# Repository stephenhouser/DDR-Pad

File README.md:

---
category: woodworking
---

## Todo

- √ Clear acrylic ~ 12x12x 0.354 @ 10 = 180 + $50 shipping
 - https://www.tapplastics.com/product/plastics/cut_to_size_plastic/polycarbonate_sheets/516
 - 2024/01/01 - orderd 10 11x11x0.354" (3/8")
 - $229.94
- √ M6 Screws, M6 Nylon nuts -- Granger
 - 2024/01/03 Picked up nuts, screws on backorder to 2024/01/08
 - $60
	
- Decals ~ $70
 - https://www.bannerbuzz.com/clear-window-decals/p

- Arduino/teensy -- will it be fast enough?
 - perhaps microcontrollers at each pad sending data and lights?

- Metal corners?
 - 16 gague, need sheet brake (Rex?)

- 1.25" SteelTex no-thread pipe -- will it be sturdy enough
 - 1.25 is only in silver color
 - 2 bases, 2 90-deg, 3 poles

## The Build we are working from

- The hardware: [DIY Arcade DDR Metal Dance Pad With LED Under $500](https://www.instructables.com/DIY-Arcade-DDR-Metal-Dance-Pad-With-LED-Under-500/)
- The electronics: [6 Panel DDR USB Controller With LED](https://www.instructables.com/6-Panel-DDR-USB-Controller-With-LED/)

## Other Builds

- [Mystic Steps build](https://www.mysticsteps.com/diy-pad/), uses a AtMega32U (32u chipset for USB I imagine)
- [andrewhlu's build](https://andrewhlu.com/ddr/), uses [STM32L476G board](https://www.digikey.com/en/products/detail/stmicroelectronics/STM32L476G-DISCO/5344355)
- [Sensor Channels](https://www.thingiverse.com/thing:4547247) on Thingiverse, replacements for original DDR

## Making Pads

- https://www.hackmycab.com/?portfolio=arrow-panels-part-1-making-new-polycarb-panels
- https://www.hackmycab.com/?portfolio=arrow-panels-part-2-arrow-decals

## Lights

- [8x6 Lights](https://ddrpad.com/collections/arcade-parts/products/arcade-pad-led-light-mod) for original DDR
- [8x8 addressable LED modules](https://www.amazon.com/WS2812B-Flexible-Individually-Addressable-64Pixels/dp/B09KBZT6LD/ref=sr_1_4?crid=2BYV3RSFGN8D9&keywords=addressable%2Brgb%2Bled%2Bpanel&qid=1704314467&sprefix=addressable%2Brgb%2Bled%2Bpanel%2Caps%2C105&sr=8-4&th=1) from Amazon
 - ws2812 should be able to do about 64fps with 512 in a chain.
 - will need power injection at each row?
 - https://electronics.stackexchange.com/questions/338248/ws2812b-response-time

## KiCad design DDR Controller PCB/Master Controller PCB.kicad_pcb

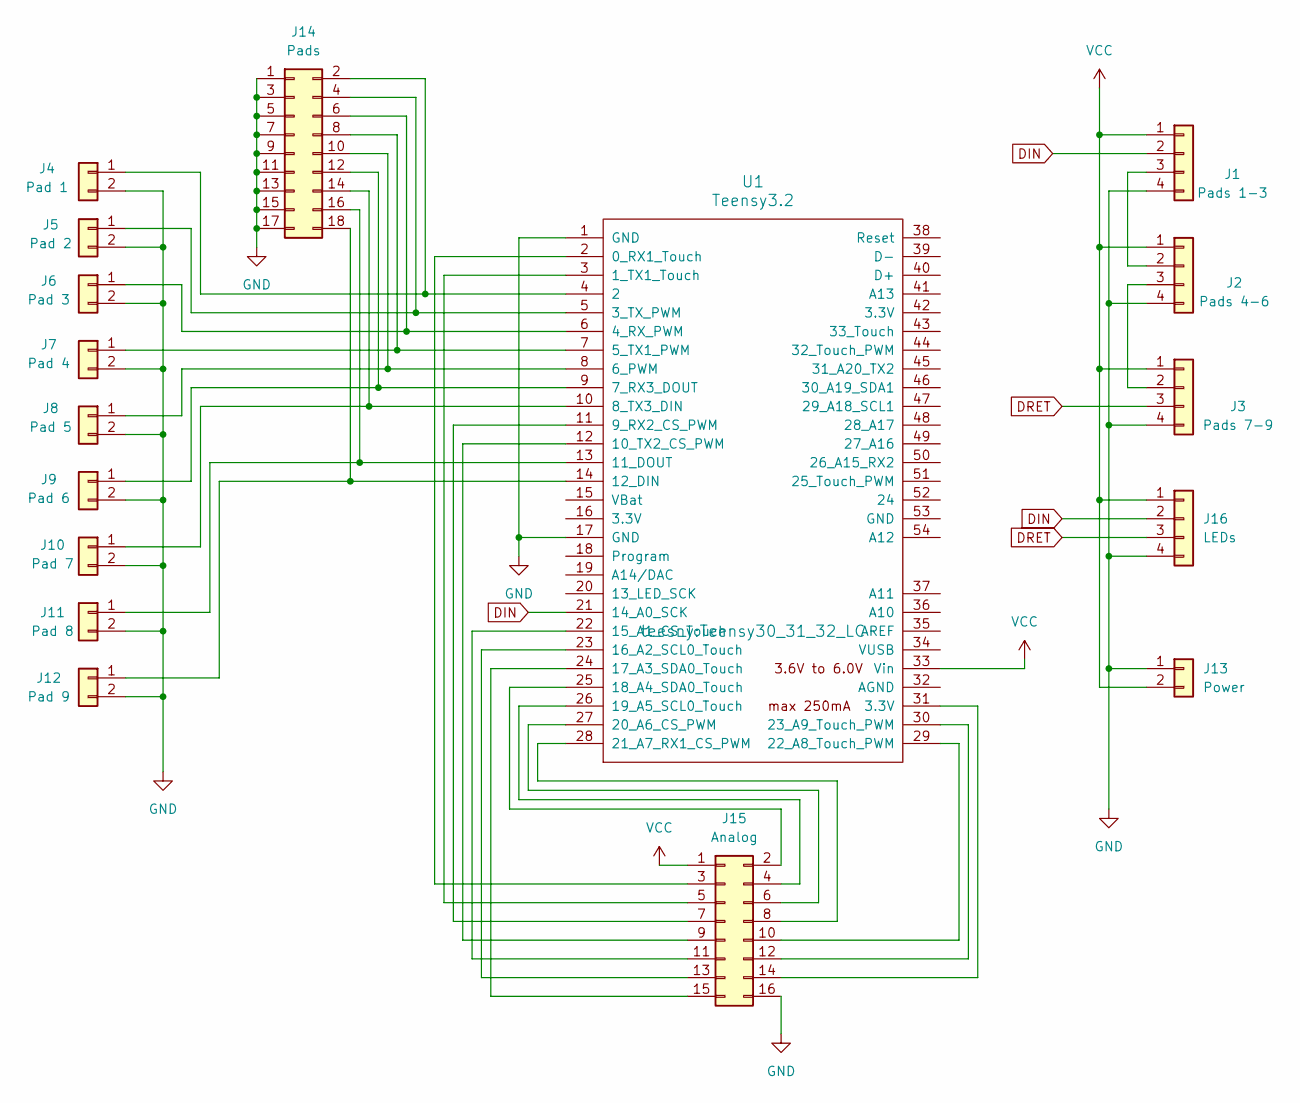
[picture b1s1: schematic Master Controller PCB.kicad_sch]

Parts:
J1: Pads 1-3; JST_XH_B4B-XH-A_1x04_P2.50mm_Vertical
J2: Pads 4-6; JST_XH_B4B-XH-A_1x04_P2.50mm_Vertical
J3: Pads 7-9; JST_XH_B4B-XH-A_1x04_P2.50mm_Vertical
J4: Pad 1; JST_XH_B2B-XH-A_1x02_P2.50mm_Vertical
J5: Pad 2; JST_XH_B2B-XH-A_1x02_P2.50mm_Vertical
J6: Pad 3; JST_XH_B2B-XH-A_1x02_P2.50mm_Vertical
J7: Pad 4; JST_XH_B2B-XH-A_1x02_P2.50mm_Vertical
J8: Pad 5; JST_XH_B2B-XH-A_1x02_P2.50mm_Vertical
J9: Pad 6; JST_XH_B2B-XH-A_1x02_P2.50mm_Vertical
J10: Pad 7; JST_XH_B2B-XH-A_1x02_P2.50mm_Vertical
J11: Pad 8; JST_XH_B2B-XH-A_1x02_P2.50mm_Vertical
J12: Pad 9; JST_XH_B2B-XH-A_1x02_P2.50mm_Vertical
J13: Power; screw_terminal_01x02_p7.62mm
J14: Pads; PinHeader_2x09_P2.54mm_Vertical
J15: Analog; PinHeader_2x08_P2.54mm_Vertical
J16: LEDs; PinHeader_1x04_P2.54mm_Vertical
U1: Teensy3.2; Teensy30_31_32_LC

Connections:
DIN: J1.2, J16.2, U1.21 (14_A0_SCK)
DRET: J3.3, J16.3
GND: J1.4, J2.4, J3.4, J4.2, J5.2, J6.2, J7.2, J8.2, J9.2, J10.2, J11.2, J12.2, J13.1, J14.1, J14.3, J14.5, J14.7, J14.9, J14.11, J14.13, J14.15, J14.17, J15.16, J16.4, U1.1 (GND), U1.17 (GND)
unnamed: J1.3, J2.2
unnamed: J2.3, J3.2
unnamed: J10.1, J14.14, U1.10 (8_TX3_DIN)
unnamed: J11.1, J14.16, U1.13 (11_DOUT)
unnamed: J12.1, J14.18, U1.14 (12_DIN)
unnamed: J4.1, J14.2, U1.4 (2)
unnamed: J5.1, J14.4, U1.5 (3_TX_PWM)
unnamed: J6.1, J14.6, U1.6 (4_RX_PWM)
unnamed: J7.1, J14.8, U1.7 (5_TX1_PWM)
unnamed: J8.1, J14.10, U1.8 (6_PWM)
unnamed: J9.1, J14.12, U1.9 (7_RX3_DOUT)
unnamed: J15.2, U1.25 (18_A4_SDA0_Touch)
unnamed: J15.3, U1.2 (0_RX1_Touch)
unnamed: J15.4, U1.26 (19_A5_SCL0_Touch)
unnamed: J15.5, U1.3 (1_TX1_Touch)
unnamed: J15.6, U1.27 (20_A6_CS_PWM)
unnamed: J15.7, U1.11 (9_RX2_CS_PWM)
unnamed: J15.8, U1.28 (21_A7_RX1_CS_PWM)
unnamed: J15.9, U1.12 (10_TX2_CS_PWM)
unnamed: J15.10, U1.29 (22_A8_Touch_PWM)
unnamed: J15.11, U1.22 (15_A1_CS_Touch)
unnamed: J15.12, U1.30 (23_A9_Touch_PWM)
unnamed: J15.13, U1.23 (16_A2_SCL0_Touch)
unnamed: J15.14, U1.31 (3.3V)
unnamed: J15.15, U1.24 (17_A3_SDA0_Touch)
VCC: J1.1, J2.1, J3.1, J13.2, J15.1, J16.1, U1.33 (Vin)

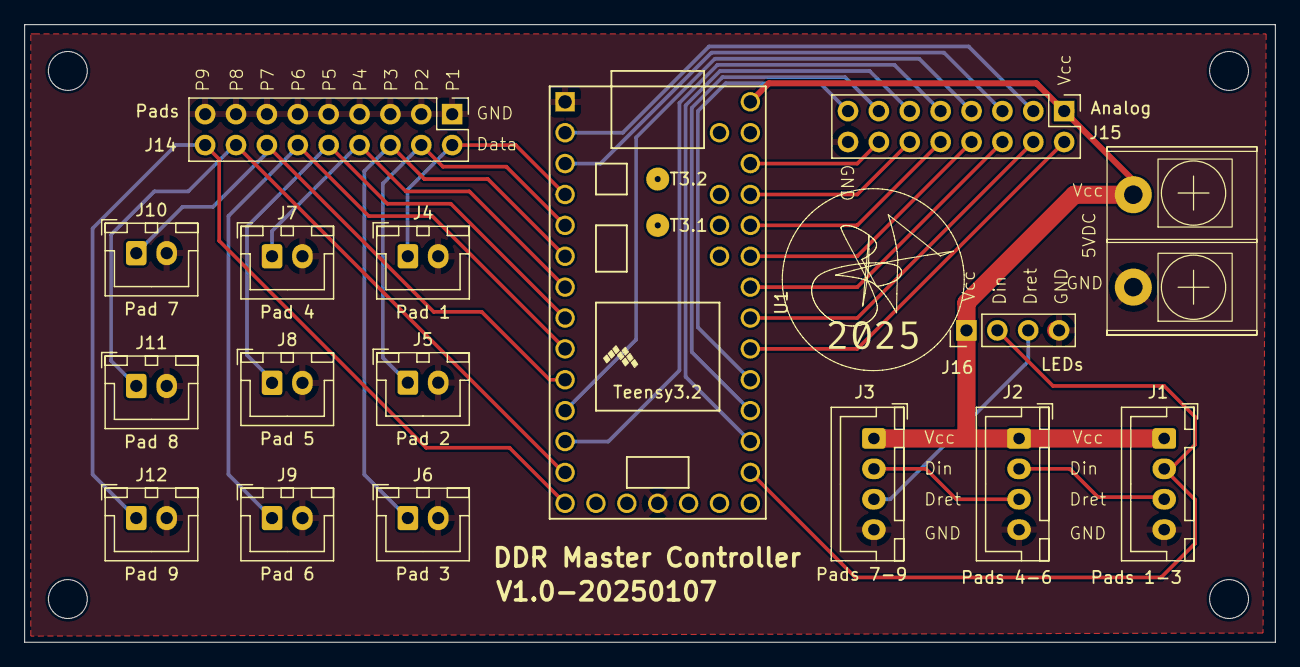
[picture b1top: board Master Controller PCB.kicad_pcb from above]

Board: 2 copper layers, 102.9 x 50.8 mm, 17 parts (0 on the bottom side), 29 nets.

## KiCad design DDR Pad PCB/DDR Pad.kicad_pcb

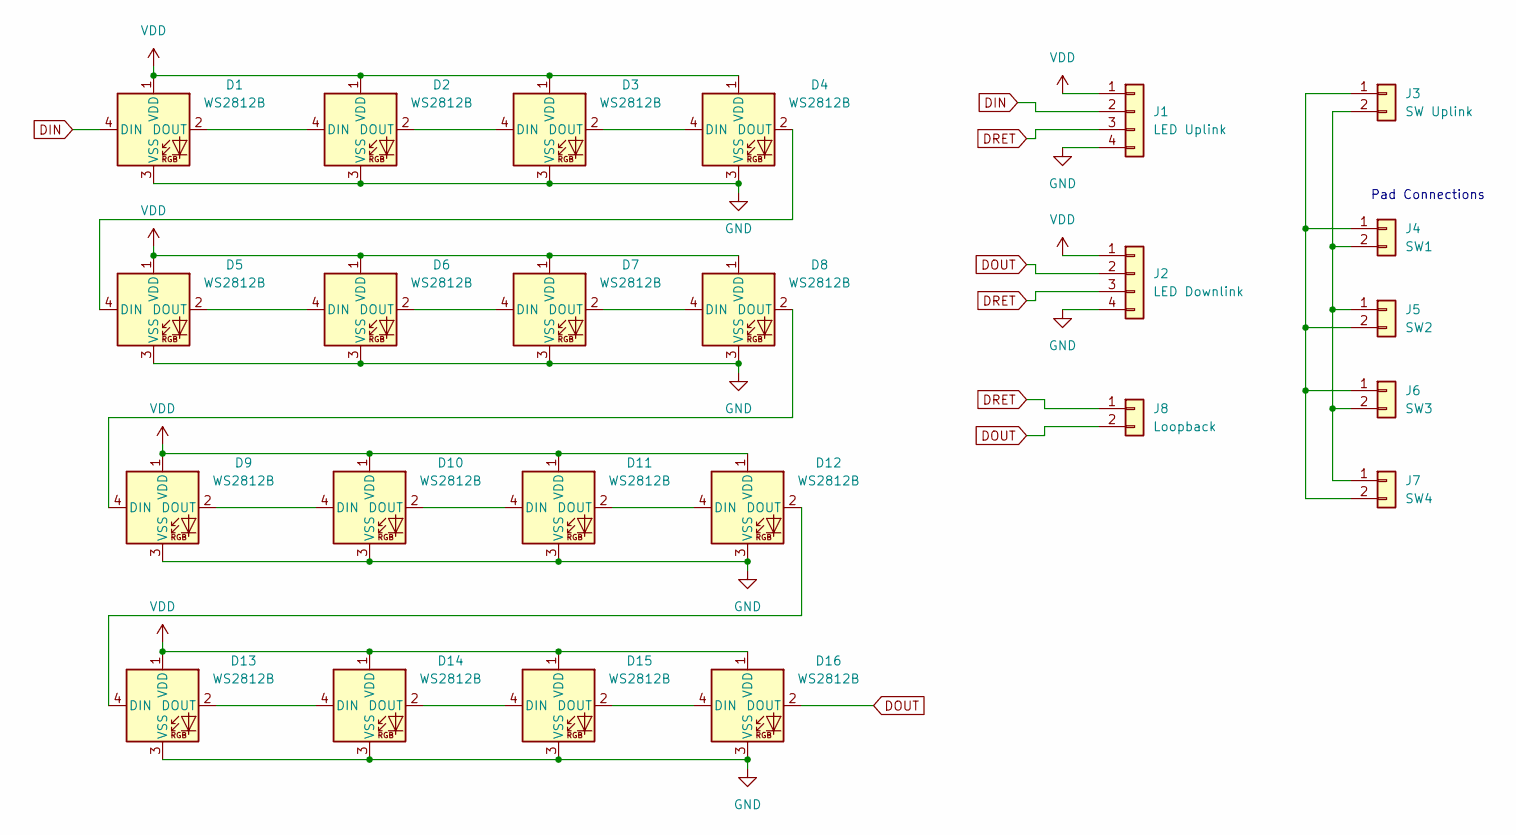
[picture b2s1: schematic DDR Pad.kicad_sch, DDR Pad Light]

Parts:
D1, D2, D3, D4, D5, D6, D7, D8, D9, D10, D11, D12, D13, D14, D15, D16: WS2812B; LED_WS2812B_PLCC4_5.0x5.0mm_P3.2mm; LCSC C2846931
J1: LED Uplink; JST_XH_S4B-XH-A_1x04_P2.50mm_Horizontal
J2: LED Downlink; JST_XH_S4B-XH-A_1x04_P2.50mm_Horizontal
J3: SW Uplink; JST_XH_S2B-XH-A-1_1x02_P2.50mm_Horizontal
J4: SW1; JST_XH_S2B-XH-A-1_1x02_P2.50mm_Horizontal
J5: SW2; JST_XH_S2B-XH-A-1_1x02_P2.50mm_Horizontal
J6: SW3; JST_XH_S2B-XH-A-1_1x02_P2.50mm_Horizontal
J7: SW4; JST_XH_S2B-XH-A-1_1x02_P2.50mm_Horizontal
J8: Loopback; PinHeader_1x02_P2.54mm_Vertical

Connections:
DIN: D1.4 (DIN), J1.2
DOUT: D16.2 (DOUT), J2.2, J8.2
DRET: J1.3, J2.3, J8.1
GND: D1.3 (VSS), D2.3 (VSS), D3.3 (VSS), D4.3 (VSS), D5.3 (VSS), D6.3 (VSS), D7.3 (VSS), D8.3 (VSS), D9.3 (VSS), D10.3 (VSS), D11.3 (VSS), D12.3 (VSS), D13.3 (VSS), D14.3 (VSS), D15.3 (VSS), D16.3 (VSS), J1.4, J2.4
unnamed: D1.2 (DOUT), D2.4 (DIN)
unnamed: D2.2 (DOUT), D3.4 (DIN)
unnamed: D3.2 (DOUT), D4.4 (DIN)
unnamed: D4.2 (DOUT), D5.4 (DIN)
unnamed: D5.2 (DOUT), D6.4 (DIN)
unnamed: D6.2 (DOUT), D7.4 (DIN)
unnamed: D7.2 (DOUT), D8.4 (DIN)
unnamed: D8.2 (DOUT), D9.4 (DIN)
unnamed: D9.2 (DOUT), D10.4 (DIN)
unnamed: D10.2 (DOUT), D11.4 (DIN)
unnamed: D11.2 (DOUT), D12.4 (DIN)
unnamed: D12.2 (DOUT), D13.4 (DIN)
unnamed: D13.2 (DOUT), D14.4 (DIN)
unnamed: D14.2 (DOUT), D15.4 (DIN)
unnamed: D15.2 (DOUT), D16.4 (DIN)
unnamed: J3.1, J4.1, J5.2, J6.1, J7.2
unnamed: J3.2, J4.2, J5.1, J6.2, J7.1
VDD: D1.1 (VDD), D2.1 (VDD), D3.1 (VDD), D4.1 (VDD), D5.1 (VDD), D6.1 (VDD), D7.1 (VDD), D8.1 (VDD), D9.1 (VDD), D10.1 (VDD), D11.1 (VDD), D12.1 (VDD), D13.1 (VDD), D14.1 (VDD), D15.1 (VDD), D16.1 (VDD), J1.1, J2.1

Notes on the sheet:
Pad Connections

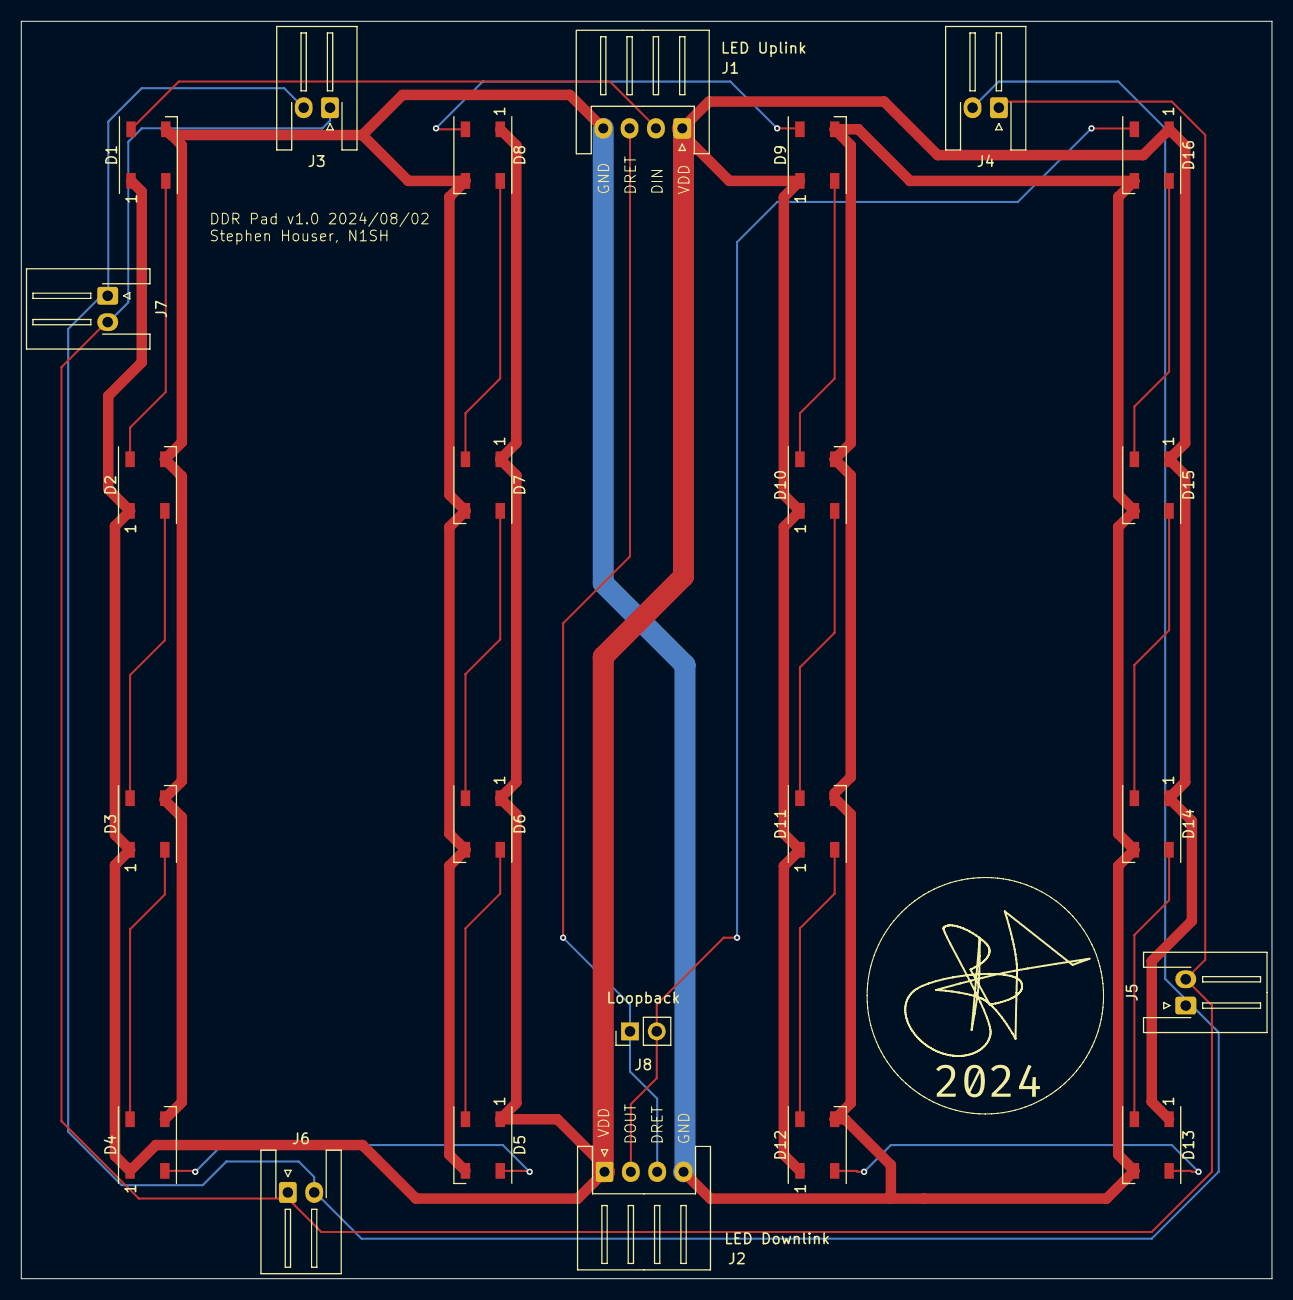
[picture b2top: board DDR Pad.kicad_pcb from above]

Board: 2 copper layers, 118.7 x 119.4 mm, 24 parts (0 on the bottom side), 22 nets.

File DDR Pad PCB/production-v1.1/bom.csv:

Designator,Footprint,Quantity,Value,LCSC Part #
"D1, D10, D11, D12, D13, D14, D15, D16, D2, D3, D4, D5, D6, D7, D8, D9",LED_WS2812B_PLCC4_5.0x5.0mm_P3.2mm,16,WS2812B,C2843785

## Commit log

2025-01-06 add readme for controller test
2025-01-07 teensy based controller that acts as a keyboard
2025-02-17 update pins for production version
2025-02-18 tweak delay for more consistent work
2025-02-24 increase brightness
2025-03-01 update code to use toggle on 17 for 4 or 9 pads
2025-03-01 rename, reorganize
2025-03-13 change to teensy 4.0
